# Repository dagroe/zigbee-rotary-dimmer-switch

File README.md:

# A rotary Zigbee dimmer switch
A Zigbee dimmer switch with a tactile feeling like classic rotary dimmers that seamlessly integrates with your existing switch and socket design lines (e.g. Gira System 55).

|   |   |
|---|---|

## Use case, requirements, and features
The goal of this dimmer switch is to
* provide tactile feeling like classic rotary dimmers, i.e. rotate and push one big knob (instead of multiple buttons)
* integrate with existing switch and socket design lines (e.g. Gira System 55), also for multi frames
* offer an optional 230V (or 110V) power supply, no more changing batteries + acts as Zigbee router
* control existing smart lights (e.g. Philips Hue), not making classic bulbs smart (i.e. switching/dimming classic bulbs)

Also nice to have:
* be extendable, e.g. easily add multiple dimmer switches or push buttons in multi frames
* ✅ allow for a second rotary input by rotating the knob while pushing it (e.g. to change color temperature or scenes) — _implemented: push + rotate changes color temperature_
* ✅ feature an integrated 230V (or 110V) mechanical switch to switch power of the connected lamp socket (e.g. for emergencies or to reset the lamp when replacing classic wall switches) — _implemented: on-board relay + dedicated button_
* be affordable

## Backstory: Why yet _another_ Zigbee dimmer switch?
TL;DR; I couldn't find one to fit my use case, so I decided to build my own.

When I moved into my new home I already had many Philips Hue Bulbs and classic Hue dimmer switches (the on with the four buttons) to control the lights.
However, those didn't integrate well with my Gira System 55 outlets, switches, frames, etc. even when using fancy adapters (https://www.samotech.co.uk/products/philips-hue-dimmer-frame-cover-light-switch/)
And I was also a big fan of using a rotary knob for dimming lights, since it is just more convenient.

So why didn't I use available rotary zigbee dimmers? Basically all dimmers I found are "real" dimmers, in the sense that they expect to control a load (classic dimmable bulb) or simply don't fit into the 55mm Gira system.

Since I though "well, it can't be that hard to hook up a rotary encoder to a Zigbee chip", I set out to build a rotary dimmer switch myself.

## Current state of development
A working second prototype is built around the **ESP32-C6**. It joins any standard Zigbee coordinator (zigbee2mqtt, Home Assistant ZHA, deCONZ, …) as a mains-powered **Zigbee router** and controls bound smart lights with a single rotary knob. Hardware, firmware, and enclosure design files are all in this repository. It is a DIY prototype, not a finished product — see [Help wanted](#help-wanted).

### Hardware
- **ESP32-C6-MINI** module (Zigbee/Thread radio), programmed/powered over USB-C.
- Integrated **230V → 5V** power supply (IRM-02-5S) plus a 3.3V regulator — no batteries, and it acts as a Zigbee router.
- **Rotary encoder with push** (the single "big knob") for dimming and on/off.
- **WS2812B RGB LED** for status/feedback.
- On-board **230V relay** (on a normally-closed contact) to switch the connected lamp socket directly, with a dedicated button to toggle it.
- A separate commissioning button for pairing / factory reset.
- Two **external daughterboard ports** so the in-wall module can drive a second control surface: a port for an external rotary encoder (a second dimmer) and a port for a plain wall switch. Both are optional — when nothing is wired in they idle and stay unused.
- Designed to fit **Gira System 55** frames.

### Controls
| Input | Action |
| ----- | ------ |
| Rotate knob | Brightness up / down (bound lights) |
| Push knob — short tap | Toggle on / off |
| Push knob — hold | Off |
| Push **and** rotate | Color temperature (warm / cool) |
| Relay button — tap | Cut / restore the 230V outlet (works even with no network) |
| External encoder (optional) | Second, independently bindable dimmer — same controls as the knob |
| External wall switch (optional) | Toggle on / off for its own independently bound light |
| Commission button — tap | Pair (start network steering) |
| Commission button — hold ~5 s | Factory reset (yellow warning while holding, red on reset) |

LED feedback: green = joined · solid red = not connected · white blink = command sent · red blink = command dropped (not joined) · blue blink = relay toggled · yellow = pairing / reset warning.

### Firmware
Built with **ESP-IDF** and the **esp-zigbee-sdk**. From `firmware/`:
```
idf.py set-target esp32c6
idf.py build
idf.py -p <PORT> flash monitor
```
After the first flash, firmware updates are delivered **over the air** (standard Zigbee OTA, with automatic rollback of a bad image). The single source of truth for the version is `firmware/main/version.h`.

### Repository layout
- `hardware/` — KiCad schematics, PCB, and exported gerbers/3D models.
- `firmware/` — ESP-IDF project ([`firmware/docs/OTA.md`](firmware/docs/OTA.md), [`firmware/z2m/README.md`](firmware/z2m/README.md), `firmware/TODO.md`).
- `enclosure/` — printable enclosure / knob design files.

## zigbee2mqtt integration & over-the-air updates
The dimmer joins any standard Zigbee coordinator and exposes four endpoints: the on-board **controller** (endpoint 1) that sends on/off, brightness and color commands to bound lights, the on-board **230V relay** (endpoint 2) to switch the connected lamp socket directly, and the two optional daughterboard ports — an **external encoder** (endpoint 3, a second dimmer) and an **external wall switch** (endpoint 4). Each controller endpoint is bound independently, so they act as separate controllers sharing one device card. It also implements the standard Zigbee OTA Upgrade cluster, so firmware updates are delivered over the air. To add the device to zigbee2mqtt and receive OTA updates from this repo, follow [`firmware/z2m/README.md`](firmware/z2m/README.md). Firmware-side OTA details (partitioning, rollback) are in [`firmware/docs/OTA.md`](firmware/docs/OTA.md).

## Help wanted
My prototype is working but I see a lot of potential for improvement. Since I am mostly a software engineer with limited knowledge of electronics, I am looking for other interested in taking this project further. You can find me on discord here: https://discord.gg/CjbDc5nPja or checkout the discussion here: https://community.home-assistant.io/t/diy-zigbee-rotary-wall-dimmer/681751

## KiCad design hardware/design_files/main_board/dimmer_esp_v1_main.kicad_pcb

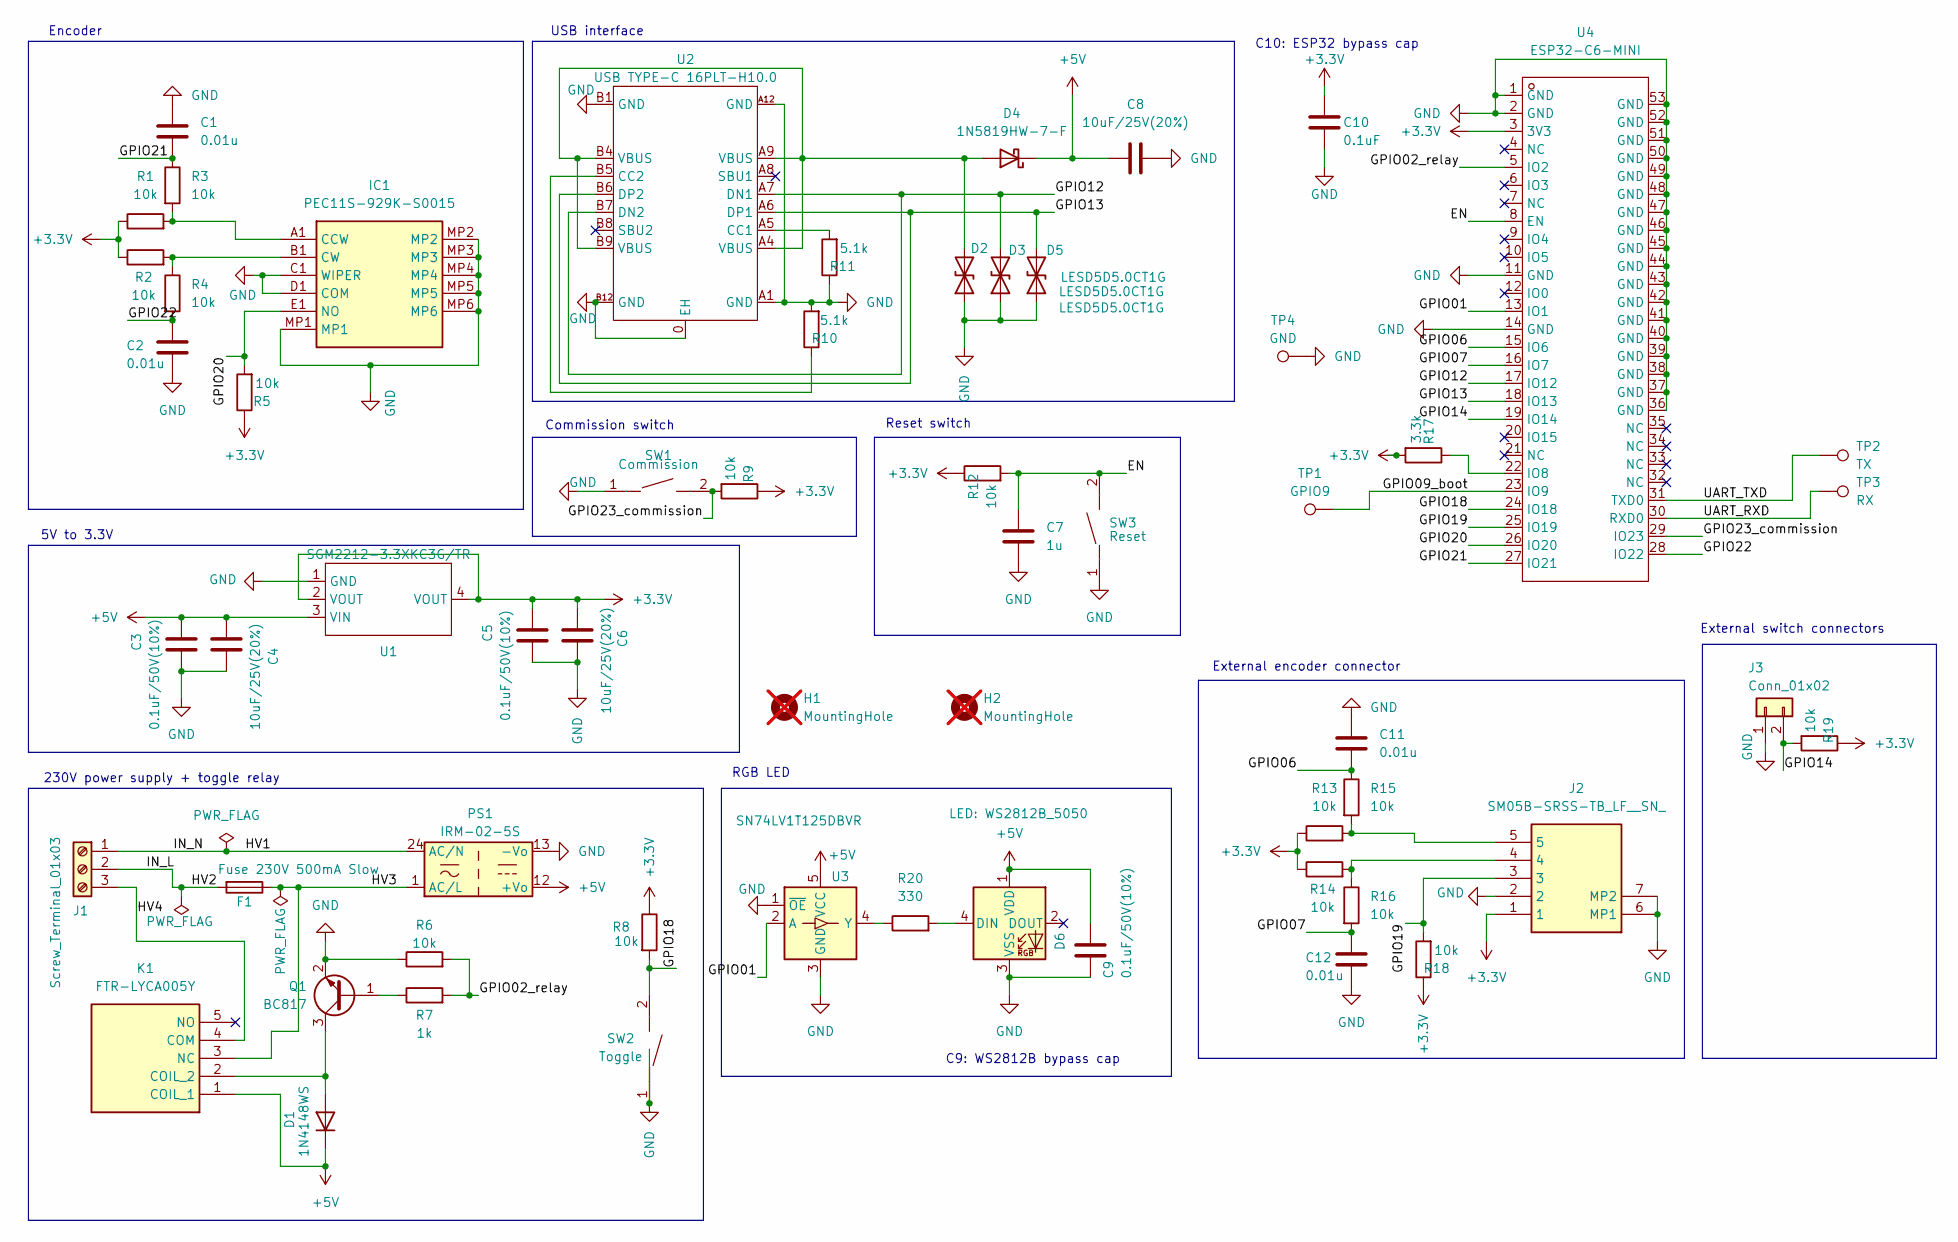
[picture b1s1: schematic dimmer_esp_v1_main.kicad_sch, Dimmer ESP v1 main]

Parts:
C1, C2, C11, C12: 0.01u; C_0603_1608Metric; MPN 0603B103K500NT; LCSC C57112
C3, C5: 0.1uF/50V(10%); C_0603_1608Metric; MPN CT41G-0603-2X1-50V-0.1uF-K(N); LCSC C125205
C4, C6, C8: 10uF/25V(20%); C_Elec_4x5.4; MPN MVK25V10M4*5 4.0TP; LCSC C371122
C7: 1u; C_0603_1608Metric; MPN CL10A105KB8NNNC; LCSC C15849
C9: 0.1uF/50V(10%); C_0603_1608Metric; LCSC C125205
C10: 0.1uF; C_0603_1608Metric; MPN CC0603KRX7R9BB104; LCSC C14663
D1: 1N4148WS; D_SOD-323; MPN 1N4148WS; LCSC C2128
D2, D3, D5: LESD5D5.0CT1G; D_SOD-523; MPN BNLESD5D5.0CT1G; LCSC C20416613
D4: 1N5819HW-7-F; D_SOD-123; MPN 1N5819HW-7-F; LCSC C82544
D6: LED: WS2812B_5050; LED_WS2812B_PLCC4_5.0x5.0mm_P3.2mm; MPN XL-5050RGBC-2812B; LCSC C2843785
F1: Fuse 230V 500mA Slow; 0443.500DR; MPN 0443.500DR; LCSC C315874
H1, H2: MountingHole; MountingHole_2.2mm_M2_DIN965; not fitted
IC1: PEC11S-929K-S0015; PEC11S929KS0015; Mouser Part Number 652-PEC11S929K-S0015
J1: Screw_Terminal_01x03; TerminalBlock_Phoenix_MKDS-1,5-3-5.08_1x03_P5.08mm_Horizont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; MPN 1715734; LCSC C480520
J2: SM05B-SRSS-TB_LF__SN_; JST_SH_SM05B-SRSS-TB_1x05-1MP_P1.00mm_Horizontal; Manufacturer_Part_Number SM05B-SRSS-TB(LF)(SN); LCSC C136657
J3: Conn_01x02; JST_SH_SM02B-SRSS-TB_1x02-1MP_P1.00mm_Horizontal; MPN SM02B-SRSS-TB(LF)(SN); LCSC C160402
K1: FTR-LYCA005Y; FTRLYCA024Y; Mouser Part Number 817-FTR-LYCA005Y
PS1: IRM-02-5S; Converter_ACDC_MeanWell_IRM-02-xx_SMD; MPN IRM-02-5S; LCSC C7211217
Q1: BC817; SOT-23; MPN BC817-40,215; LCSC C52801
R1, R2, R3, R4, R5, R6, R8, R9, R12, R13, R14, R15, R16, R18, R19: 10k; R_0603_1608Metric; MPN 0603WAF1002T5E; LCSC C25804
R7: 1k; R_0603_1608Metric; MPN 0603WAF1001T5E; LCSC C21190
R10, R11: 5.1k; R_0603_1608Metric; MPN 0603WAF5101T5E; LCSC C23186
R17: 3.3k; R_0603_1608Metric; MPN 0603WAF3301T5E; LCSC C22978
R20: 330; R_0603_1608Metric; MPN 0603WAF3300T5E; LCSC C23138
SW1: Commission; SW-SMD_L3.9-W3.0-P4.45; Manufacturer Part TS-1088-AR02016; LCSC Part Name 4*3*2mm 立贴 轻触开关
SW2: Toggle; SW-SMD_L3.9-W3.0-P4.45; Manufacturer Part TS-1088-AR02016; LCSC Part Name 4*3*2mm 立贴 轻触开关
SW3: Reset; SW-SMD_L3.9-W3.0-P4.45; Manufacturer Part TS-1088-AR02016; LCSC Part Name 4*3*2mm 立贴 轻触开关
TP1: GPIO9; TestPoint_Pad_D1.5mm
TP2: TX; TestPoint_Pad_D1.5mm
TP3: RX; TestPoint_Pad_D1.5mm
TP4: GND; TestPoint_Pad_D1.5mm
U1: SGM2212-3.3XKC3G/TR; SOT-223-3_L6.5-W3.4-P2.30-LS7.0-BR; Manufacturer Part SGM2212-3.3XKC3G/TR; LCSC Part Name SGM2212-3.3XKC3G/TR
U2: USB TYPE-C 16PLT-H10.0; TYPE-C-SMD_USB4120-03-C; Manufacturer Part TYPE-C 16PLT-H10.0; LCSC Part Name Type-C 母 立贴
U3: SN74LV1T125DBVR; SOT-23-5; MPN SN74LV1T125DBVR; LCSC C473338
U4: ESP32-C6-MINI; WIFIM-SMD_61P-L16.6-W13.2-P0.80-ESP32-C6-MINI-1-N4; Manufacturer Part ESP32-C6-MINI-1-N4; LCSC Part Name ESP32-C6-MINI-1-N4

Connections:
+3.3V: C5.2, C6.1, C10.1, J2.1, R1.1, R2.1, R5.1, R8.1, R9.1, R12.1, R13.1, R14.1, R17.2, R18.1, R19.1, U1.2 (VOUT), U1.4 (VOUT), U4.3 (3V3)
+5V: C3.2, C4.1, C8.1, C9.1, D1.1 (K), D4.1 (K), D6.1 (VDD), K1.1 (COIL_1), PS1.12 (+Vo), U1.3 (VIN), U3.5 (VCC)
/EN: C7.2, R12.2, SW3.2, U4.8 (EN)
/GPIO01: U3.2 (A), U4.13 (IO1)
/GPIO02_relay: R6.2, R7.2, U4.5 (IO2)
/GPIO06: C11.2, R15.1, U4.15 (IO6)
/GPIO07: C12.2, R16.2, U4.16 (IO7)
/GPIO09_boot: TP1.1 (1_1), U4.23 (IO9)
/GPIO12: D3.2 (A2), U2.A7 (DN1), U2.B7 (DN2), U4.17 (IO12)
/GPIO13: D5.2 (A2), U2.A6 (DP1), U2.B6 (DP2), U4.18 (IO13)
/GPIO14: J3.2, R19.2, U4.19 (IO14)
/GPIO18: R8.2, SW2.2, U4.24 (IO18)
/GPIO19: J2.3, R18.2, U4.25 (IO19)
/GPIO20: IC1.E1 (NO), R5.2, U4.26 (IO20)
/GPIO21: C1.2, R3.1, U4.27 (IO21)
/GPIO22: C2.2, R4.2, U4.28 (IO22)
/GPIO23_commission: R9.2, SW1.2, U4.29 (IO23)
/HV1: J1.1, PS1.24 (AC/N)
/HV2: F1.2, J1.2
/HV3: F1.1, K1.3 (NC), PS1.1 (AC/L)
/HV4: J1.3, K1.4 (COM)
/UART_RXD: TP3.1 (1_1), U4.30 (RXD0)
/UART_TXD: TP2.1 (1_1), U4.31 (TXD0)
GND: C1.1, C2.1, C3.1, C4.2, C5.1, C6.2, C7.1, C8.2, C9.2, C10.2, C11.1, C12.1, D2.1 (A1), D3.1 (A1), D5.1 (A1), D6.3 (VSS), IC1.C1 (WIPER), IC1.D1 (COM), IC1.MP1, IC1.MP2, IC1.MP3, IC1.MP4, IC1.MP5, IC1.MP6, J2.2, J2.6 (MP1), J2.7 (MP2), J3.1, PS1.13 (-Vo), Q1.2 (E), R6.1, R10.2, R11.1, SW1.1, SW2.1, SW3.1, TP4.1 (1_1), U1.1 (GND), U2.0 (EH), U2.A1 (GND), U2.A12 (GND), U2.B1 (GND), U2.B12 (GND), U3.1 (~OE), U3.3 (GND), U4.1 (GND), U4.2 (GND), U4.11 (GND), U4.14 (GND), U4.36 (GND), U4.37 (GND), U4.38 (GND), U4.39 (GND), U4.40 (GND), U4.41 (GND), U4.42 (GND), U4.43 (GND), U4.44 (GND), U4.45 (GND), U4.46 (GND), U4.47 (GND), U4.48 (GND), U4.49 (GND), U4.50 (GND), U4.51 (GND), U4.52 (GND), U4.53 (GND)
unnamed: D1.2 (A), K1.2 (COIL_2), Q1.3 (C)
unnamed: D2.2 (A2), D4.2 (A), U2.A4 (VBUS), U2.A9 (VBUS), U2.B4 (VBUS), U2.B9 (VBUS)
unnamed: D6.4 (DIN), R20.2
unnamed: IC1.A1 (CCW), R1.2, R3.2
unnamed: IC1.B1 (CW), R2.2, R4.1
unnamed: J2.4, R14.2, R16.1
unnamed: J2.5, R13.2, R15.2
unnamed: Q1.1 (B), R7.1
unnamed: R11.2, U2.A5 (CC1)
unnamed: R10.1, U2.B5 (CC2)
unnamed: R20.1, U3.4 (Y)
unnamed: R17.1, U4.22 (IO8)

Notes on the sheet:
RGB LED
External encoder connector
Encoder
USB interface
Commission switch
Reset switch
5V to 3.3V
C10: ESP32 bypass cap
C9: WS2812B bypass cap
External switch connectors
230V power supply + toggle relay

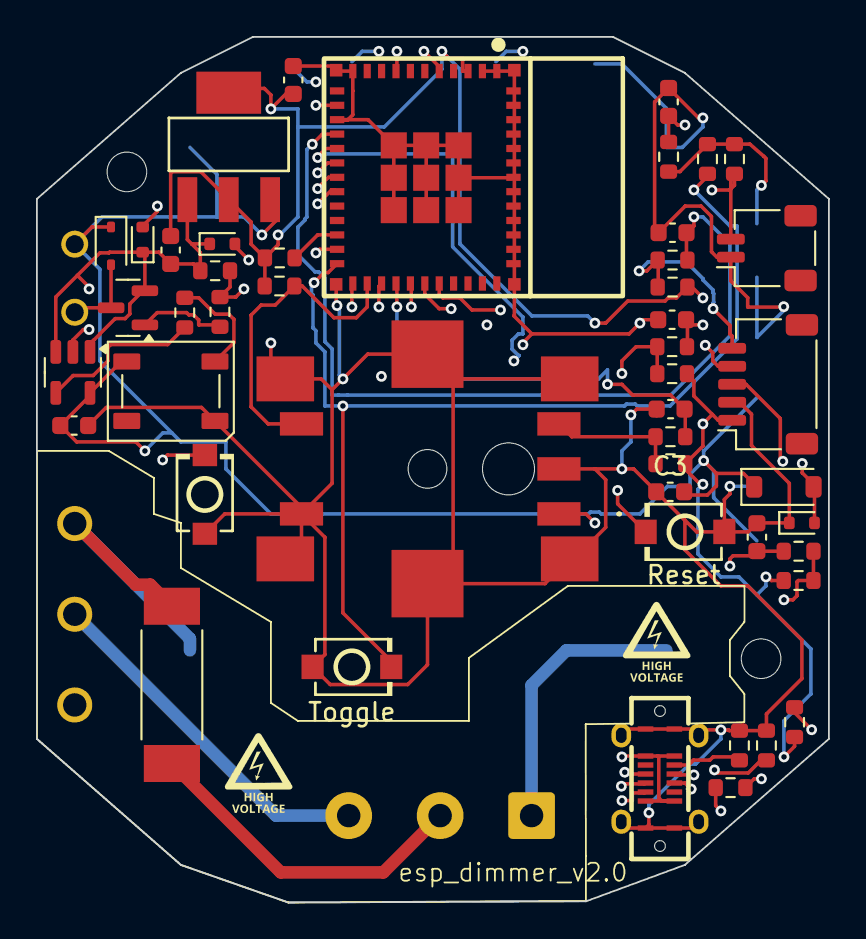
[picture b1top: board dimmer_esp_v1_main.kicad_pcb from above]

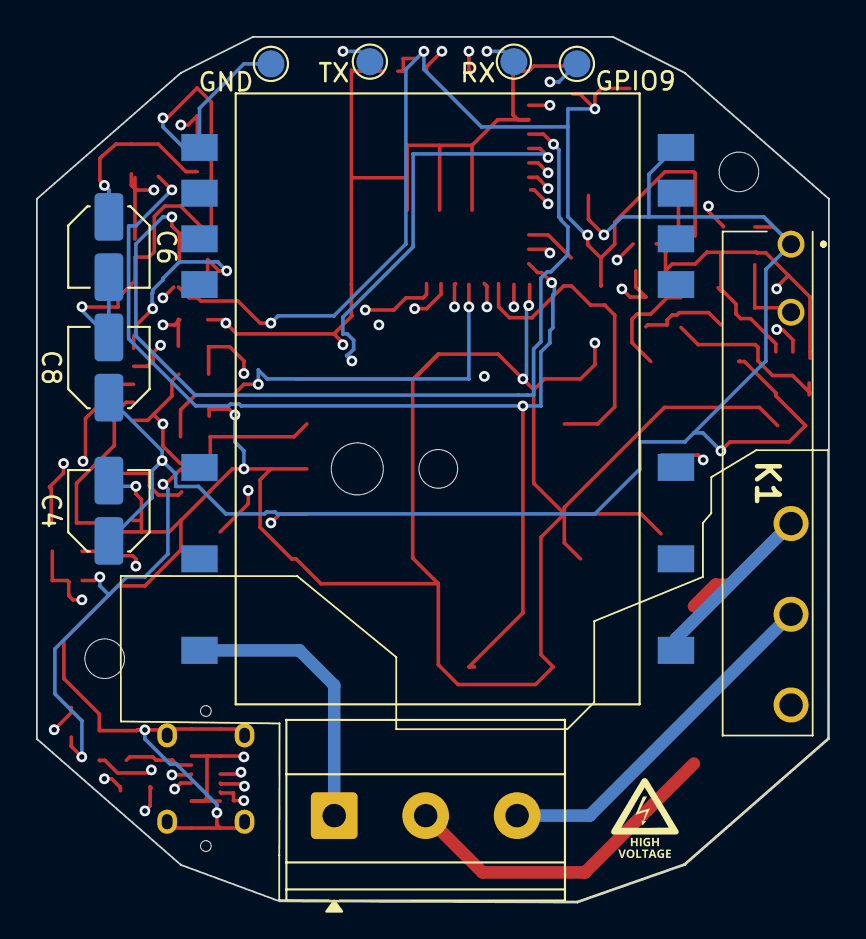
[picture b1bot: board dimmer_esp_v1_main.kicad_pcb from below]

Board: 4 copper layers, 44.0 x 48.1 mm, 59 parts (10 on the bottom side), 36 nets.

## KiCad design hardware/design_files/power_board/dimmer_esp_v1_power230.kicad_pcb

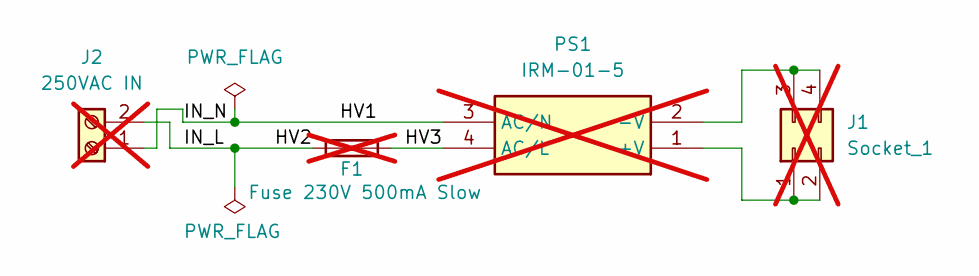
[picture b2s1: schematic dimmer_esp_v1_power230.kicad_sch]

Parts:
F1: Fuse 230V 500mA Slow; 0443.500DR; not fitted
J1: Socket_1; PinSocket_2x02_P2.54mm_Vertical; LCSC C780055; not fitted
J2: 250VAC IN; TerminalBlock_Phoenix_MKDS-1,5-2-5.08_1x02_P5.08mm_Horizont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; LCSC C91153; not fitted
PS1: IRM-01-5; IRM015; Mouser Part Number 709-IRM01-5; not fitted

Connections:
/HV1: J2.1, PS1.3 (AC/N)
/HV2: F1.2, J2.2
/HV3: F1.1, PS1.4 (AC/L)
unnamed: J1.1, J1.2, PS1.1 (+V)
unnamed: J1.3, J1.4, PS1.2 (-V)

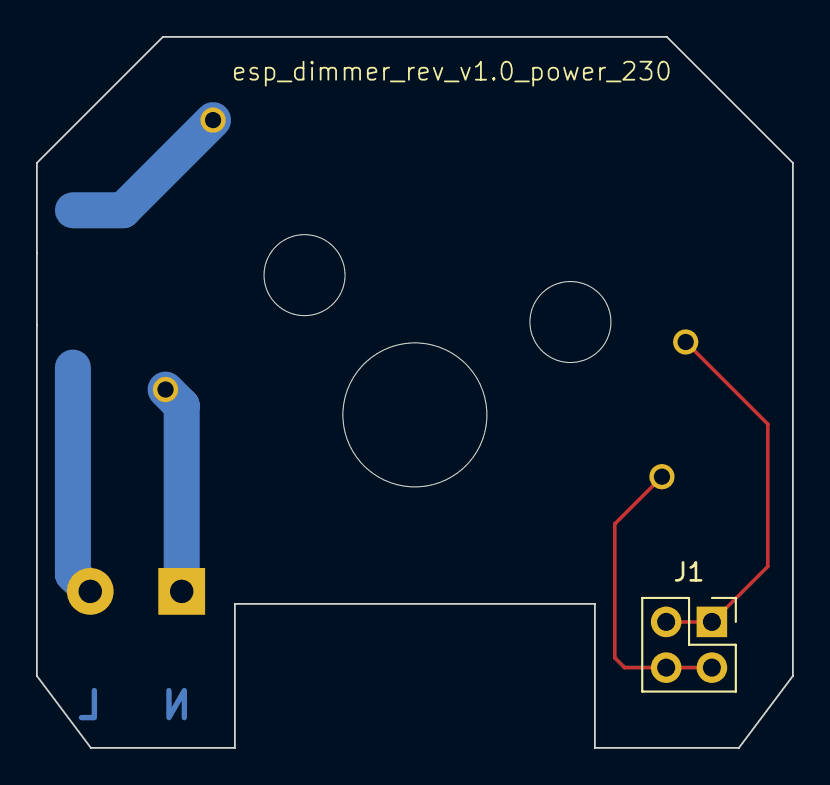
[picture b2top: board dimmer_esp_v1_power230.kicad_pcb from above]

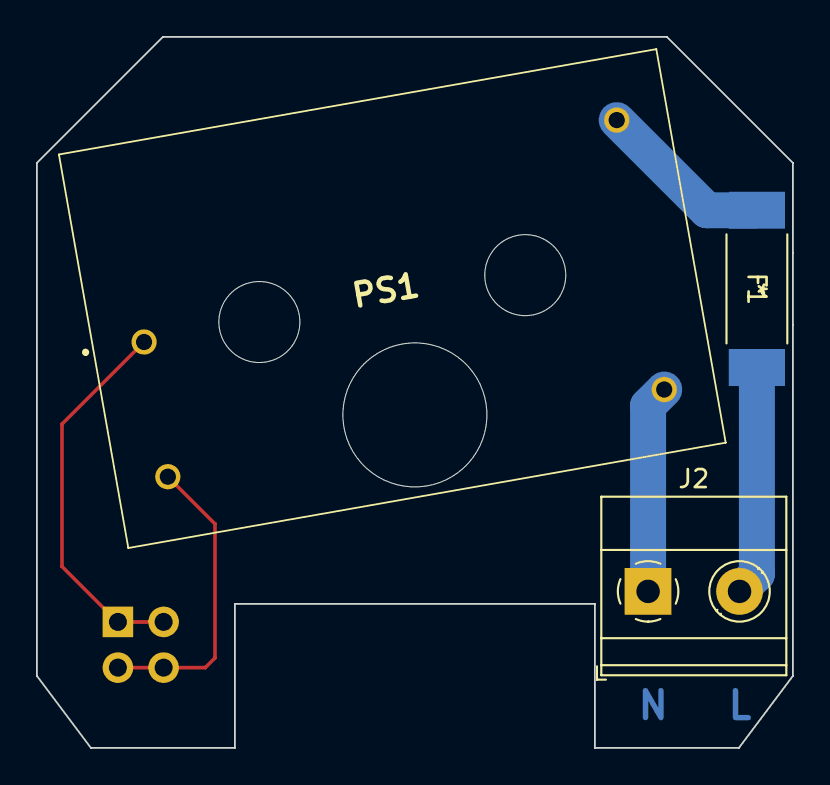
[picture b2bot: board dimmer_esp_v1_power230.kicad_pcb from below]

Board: 2 copper layers, 42.0 x 39.5 mm, 4 parts (3 on the bottom side), 5 nets.

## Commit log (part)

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2024-01-24 Add initial version of README
2024-01-29 Add images of hardware prototype
2024-11-21 Add schematics for v1 of ESP32-C6 based boards
2024-11-22 Add Kicad source files for main PCB
2024-11-22 Add Kicad source files for power PCB
2024-11-22 Add initial test for converting the enclosure fab script to openSCAD
2024-11-24 Remove unused second page from schematics
2024-11-25 Add initial openSCAD for enclosure
2025-01-08 Finish initial version of enclosure
2025-02-15 Add current firmware code from different local git repo
2025-02-15 Enclosure: Minor adjustments (add little pusher to flap above front button)
2025-05-31 Save as kicad 9.0.2, update libraries
2025-06-02 Add components, version with relay, needs re-layout of tracks
2025-06-03 Adapt pin header
2025-06-03 Add toggle circuit, arrange components on PCB
2025-06-06 Wired everything up
2025-06-06 Add circuit for external encoder
2025-06-06 Add schematics PDF
2025-06-07 Add correct USB, fix button layout
2025-06-07 Add correct relay
2025-06-07 Update schematics PDF
2025-09-15 Fix trace before remove debug interface
2025-09-15 Remove debug interface, two JST connectors, replace toggle circuit with using microcontroller
2025-10-03 Add new openScad file for ESP version enclosure
2025-10-03 Finish holes for power connector and buttons
2025-10-03 Rework PCB, switch to bigger LDO, fix distance between high and low voltage
2025-10-20 Slight adjustments to fit actual hardware
2025-10-20 Upgrade to latest ESP-IDF
2025-10-20 Prevent button up when encoder was rotated after button down
2025-10-20 Add blinking modes to LED. Blink once when rotated
2025-10-20 Fix blinking code
2025-10-22 Make encoder read half steps
2025-10-22 Enclosure: Adjustments to make USB fit and screw connectors more robust
2025-10-22 Enclosure: Add missing reference files (board outline and STL)
2025-10-27 Enclosure: Fix missing holes to access screws of 230V terminal
2025-11-10 Firmware: Move LED code into own file
2025-11-11 Replace button queue with boolean flag
2025-11-12 Fix led_driver
2026-01-12 Hardware: Add pull-down to GPIO15 to ensure JTAG via USB works
2026-01-12 Firmware: Move config into own file, add optional debug output
2026-01-27 Firmware: Fix minor issues
2026-01-27 Firmware: Fix button handling - hold & rotate
2026-04-12 Disable debug flag
2026-04-19 Add changes to PCB layout
2026-04-19 Remove bypass cap for LED for now (no space on PCB)
2026-04-19 Add MPN to components
2026-04-20 Upgrade KiCad to v10
2026-06-12 Firmware: Update zigbee stack version
2026-06-16 Hardware: Switch button pin from GPIO09 (strapping pin) to GPIO23
2026-06-16 Firmware: Update SDK config
2026-06-16 Hardware: Rename C9 back to C8, fix tracks
2026-06-16 Hardware: Switch relay pin from D15 (strapping pin) to D02
2026-06-17 Firmware: Enable auto rollback on bad OTA upgrade
2026-06-17 OTA: release firmware 1.0.3
2026-06-17 OTA: release firmware 1.1.0

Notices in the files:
parts and their libraries:
Copyright 2021 Accelerated Designs. All rights reserved.
